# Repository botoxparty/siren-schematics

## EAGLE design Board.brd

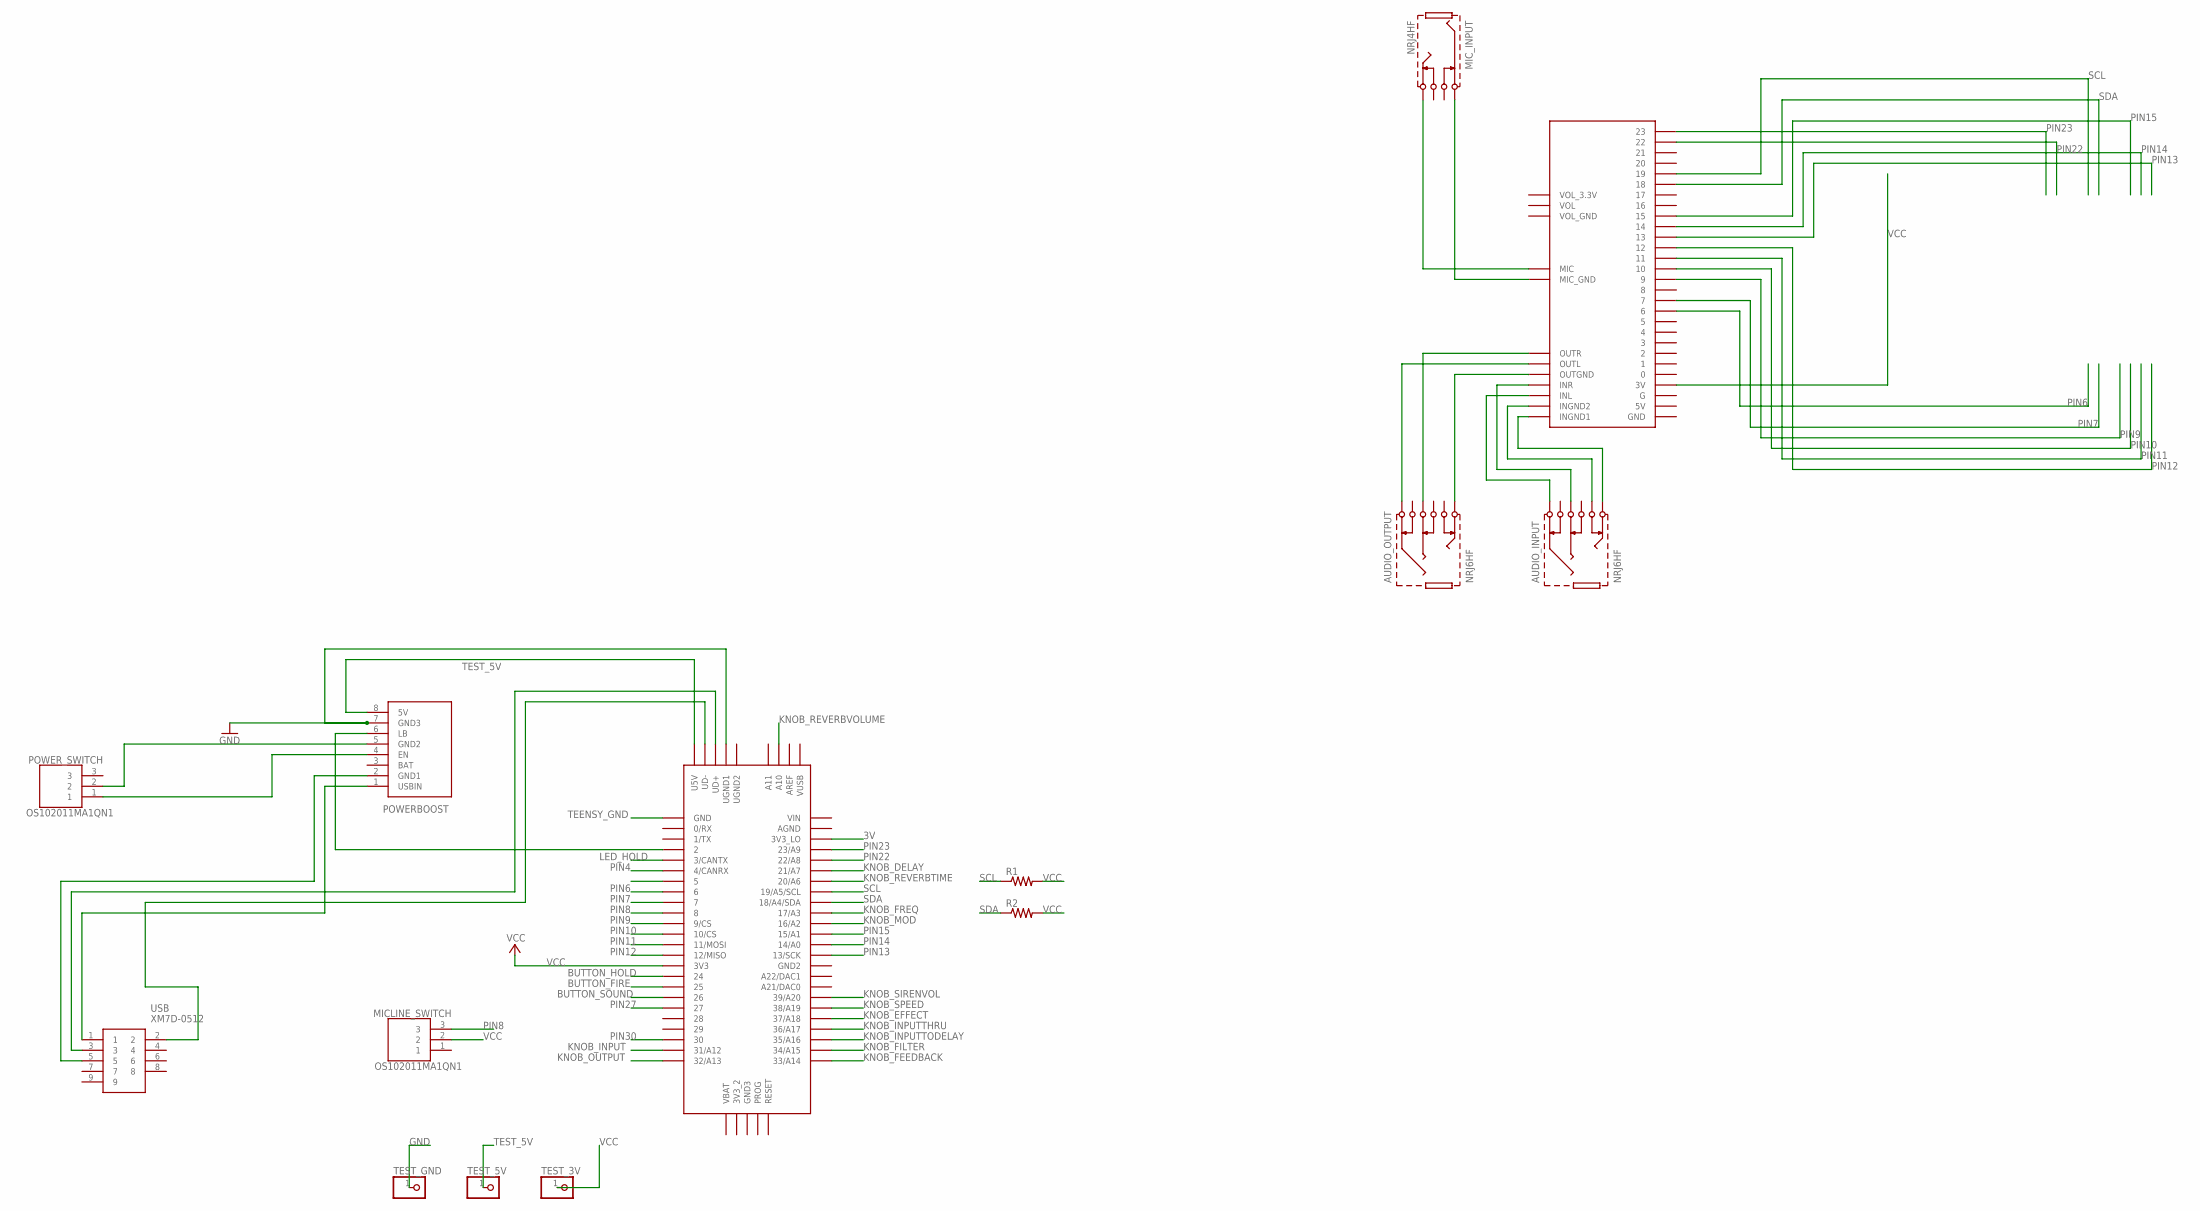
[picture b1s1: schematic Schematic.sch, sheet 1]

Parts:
AUDIO_INPUT: NRJ6HF
AUDIO_OUTPUT: NRJ6HF
MICLINE_SWITCH: OS102011MA1QN1
MIC_INPUT: NRJ4HF
POWER_SWITCH: OS102011MA1QN1
R1, R2: R-US_0207/10; 0207/10
TEENSY: TEENSY_3.5/3.6
TEST_3V, TEST_5V: PINHD-1X1; 1X01
TEST_GND: PINHD-1X1; 1X01
U$2: POWERBOOST500C; POWERBOOST500
U$5: AUDIOSHIELD
USB: XM7D-0512; XM7D0512

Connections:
3V: TEENSY.3V3_LO
BUTTON_FIRE: TEENSY.25; also elsewhere on the board
BUTTON_HOLD: TEENSY.24; also elsewhere on the board
BUTTON_SOUND: TEENSY.26; also elsewhere on the board
GND: TEENSY.UGND1, TEST_GND.1, U$2.7 (GND3); also elsewhere on the board
KNOB_DELAY: TEENSY.21/A7; also elsewhere on the board
KNOB_EFFECT: TEENSY.37/A18; also elsewhere on the board
KNOB_FEEDBACK: TEENSY.33/A14; also elsewhere on the board
KNOB_FILTER: TEENSY.34/A15; also elsewhere on the board
KNOB_FREQ: TEENSY.17/A3; also elsewhere on the board
KNOB_INPUT: TEENSY.31/A12; also elsewhere on the board
KNOB_INPUTTHRU: TEENSY.36/A17; also elsewhere on the board
KNOB_INPUTTODELAY: TEENSY.35/A16; also elsewhere on the board
KNOB_MOD: TEENSY.16/A2; also elsewhere on the board
KNOB_OUTPUT: TEENSY.32/A13; also elsewhere on the board
KNOB_REVERBTIME: TEENSY.20/A6; also elsewhere on the board
KNOB_REVERBVOLUME: TEENSY.A10; also elsewhere on the board
KNOB_SIRENVOL: TEENSY.39/A20; also elsewhere on the board
KNOB_SPEED: TEENSY.38/A19; also elsewhere on the board
LED_HOLD: TEENSY.3/CANTX; also elsewhere on the board
unnamed: U$2.1 (USBIN), USB.1
unnamed: U$2.2 (GND1), USB.5
unnamed: TEENSY.UD-, USB.2
unnamed: TEENSY.UD+, USB.3
unnamed: MIC_INPUT.SLEEVE, U$5.GND_MIC (MIC_GND)
unnamed: MIC_INPUT.TIP, U$5.MIC
unnamed: AUDIO_OUTPUT.TIP, U$5.OUTGND
unnamed: AUDIO_INPUT.SLEEVE, U$5.INL
unnamed: AUDIO_OUTPUT.RING, U$5.OUTR
unnamed: AUDIO_INPUT.TIP, U$5.INGND1
unnamed: AUDIO_INPUT.TIP-S, U$5.INGND2
unnamed: AUDIO_INPUT.RING, U$5.INR
unnamed: AUDIO_OUTPUT.SLEEVE, U$5.OUTL
unnamed: TEENSY.2, U$2.6 (LB)
unnamed: POWER_SWITCH.1, U$2.4 (EN)
unnamed: POWER_SWITCH.2, U$2.5 (GND2)
PIN4: TEENSY.4/CANRX; also elsewhere on the board
PIN5: TEENSY.5; also elsewhere on the board
PIN6: TEENSY.6, U$5.6
PIN7: TEENSY.7, U$5.7
PIN8: MICLINE_SWITCH.3, TEENSY.8
PIN9: TEENSY.9/CS, U$5.9
PIN10: TEENSY.10/CS, U$5.10
PIN11: TEENSY.11/MOSI, U$5.11
PIN12: TEENSY.12/MISO, U$5.12
PIN13: TEENSY.13/SCK, U$5.13
PIN14: TEENSY.14/A0, U$5.14
PIN15: TEENSY.15/A1, U$5.15
PIN22: TEENSY.22/A8, U$5.22
PIN23: TEENSY.23/A9, U$5.23
PIN27: TEENSY.27; also elsewhere on the board
PIN30: TEENSY.30; also elsewhere on the board
SCL: R1.1, TEENSY.19/A5/SCL, U$5.19; also elsewhere on the board
SDA: R2.1, TEENSY.18/A4/SDA, U$5.18; also elsewhere on the board
TEENSY_GND: TEENSY.GND
TEST_5V: TEENSY.U5V, TEST_5V.1, U$2.8 (5V)
VCC: MICLINE_SWITCH.2, R1.2, R2.2, TEENSY.3V3, TEST_3V.1, U$5.3V; also elsewhere on the board

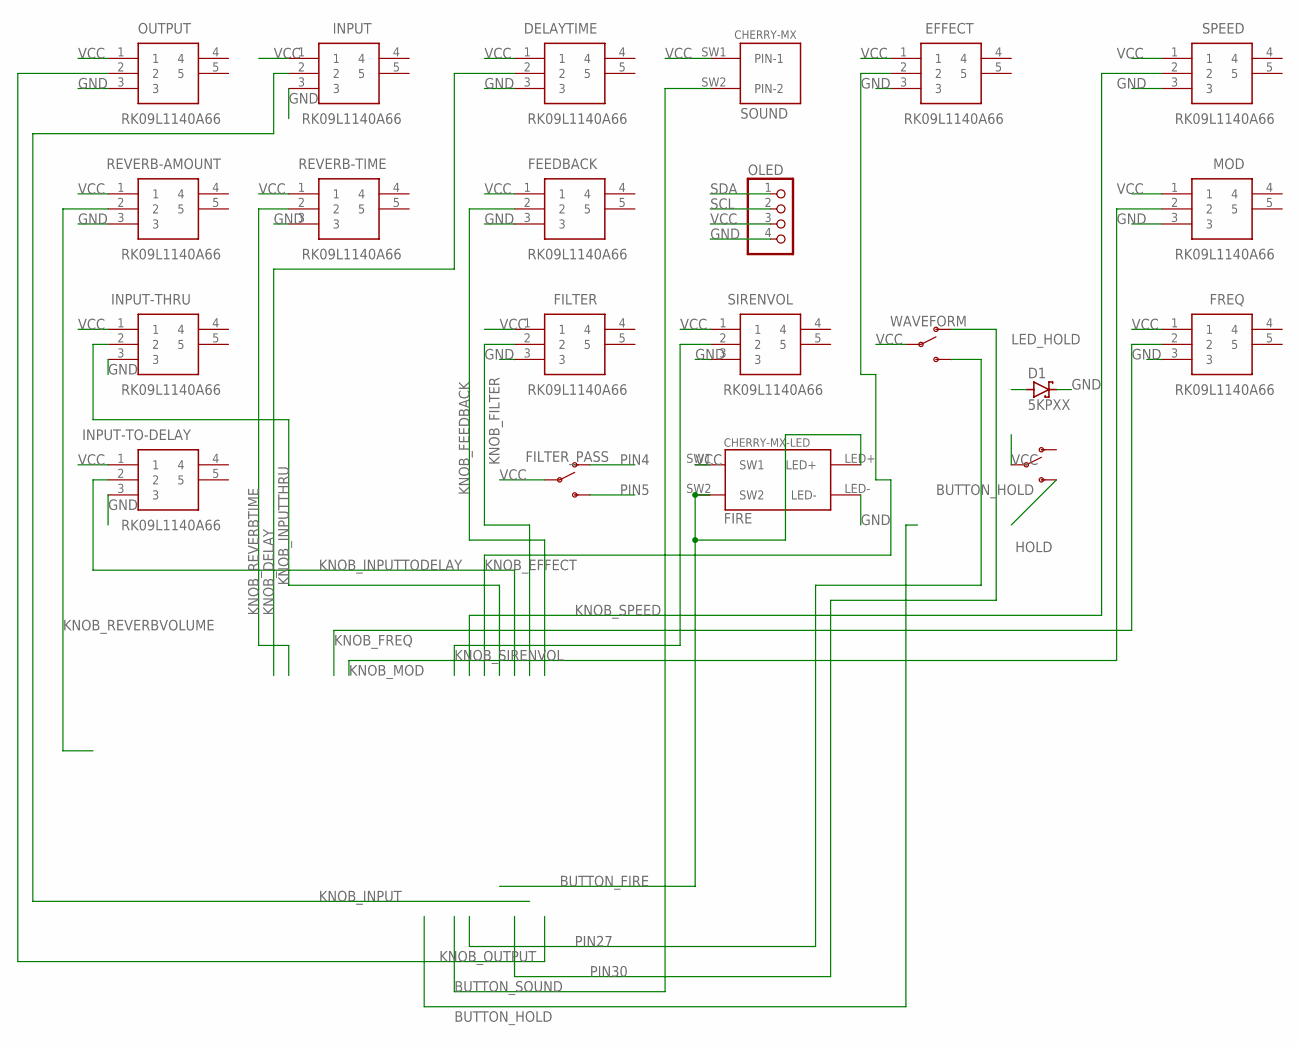
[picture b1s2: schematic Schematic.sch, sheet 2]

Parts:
D1: 5KPXX; P6T15
DELAYTIME: RK09L1140A66
EFFECT: RK09L1140A66
FEEDBACK: RK09L1140A66
FILTER: RK09L1140A66
FILTER_PASS: SWITCH-SPDT-PTH-11.6X4.0MM-LOCK; SWITCH_SPDT_PTH_11.6X4.0MM_LOCK
FIRE: CHERRY-MX-LED
FREQ: RK09L1140A66
HOLD: SWITCH-SPDT-PTH-11.6X4.0MM-LOCK; SWITCH_SPDT_PTH_11.6X4.0MM_LOCK
INPUT: RK09L1140A66
INPUT-THRU: RK09L1140A66
INPUT-TO-DELAY: RK09L1140A66
MOD: RK09L1140A66
OLED: PINHD-1X4; 1X04
OUTPUT: RK09L1140A66
REVERB-AMOUNT: RK09L1140A66
REVERB-TIME: RK09L1140A66
SIRENVOL: RK09L1140A66
SOUND: CHERRY-MX
SPEED: RK09L1140A66
WAVEFORM: SWITCH-SPDT-PTH-11.6X4.0MM-LOCK; SWITCH_SPDT_PTH_11.6X4.0MM_LOCK

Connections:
BUTTON_FIRE: FIRE.LED+, FIRE.SW2; also elsewhere on the board
BUTTON_HOLD: HOLD.3 (S); also elsewhere on the board
BUTTON_SOUND: SOUND.SW2 (PIN-2); also elsewhere on the board
GND: D1.C, DELAYTIME.3, EFFECT.3, FEEDBACK.3, FILTER.3, FIRE.LED-, FREQ.3, INPUT.3, INPUT-THRU.3, INPUT-TO-DELAY.3, MOD.3, OLED.4, OUTPUT.3, REVERB-AMOUNT.3, REVERB-TIME.3, SIRENVOL.3, SPEED.3; also elsewhere on the board
KNOB_DELAY: DELAYTIME.2; also elsewhere on the board
KNOB_EFFECT: EFFECT.2; also elsewhere on the board
KNOB_FEEDBACK: FEEDBACK.2; also elsewhere on the board
KNOB_FILTER: FILTER.2; also elsewhere on the board
KNOB_FREQ: FREQ.2; also elsewhere on the board
KNOB_INPUT: INPUT.2; also elsewhere on the board
KNOB_INPUTTHRU: INPUT-THRU.2; also elsewhere on the board
KNOB_INPUTTODELAY: INPUT-TO-DELAY.2; also elsewhere on the board
KNOB_MOD: MOD.2; also elsewhere on the board
KNOB_OUTPUT: OUTPUT.2; also elsewhere on the board
KNOB_REVERBTIME: REVERB-TIME.2; also elsewhere on the board
KNOB_REVERBVOLUME: REVERB-AMOUNT.2; also elsewhere on the board
KNOB_SIRENVOL: SIRENVOL.2; also elsewhere on the board
KNOB_SPEED: SPEED.2; also elsewhere on the board
LED_HOLD: D1.A; also elsewhere on the board
PIN4: FILTER_PASS.1 (O); also elsewhere on the board
PIN5: FILTER_PASS.3 (S); also elsewhere on the board
PIN27: WAVEFORM.3 (S); also elsewhere on the board
PIN30: WAVEFORM.1 (O); also elsewhere on the board
SCL: OLED.2; also elsewhere on the board
SDA: OLED.1; also elsewhere on the board
VCC: DELAYTIME.1, EFFECT.1, FEEDBACK.1, FILTER.1, FILTER_PASS.2, FIRE.SW1, FREQ.1, HOLD.2, INPUT.1, INPUT-THRU.1, INPUT-TO-DELAY.1, MOD.1, OLED.3, OUTPUT.1, REVERB-AMOUNT.1, REVERB-TIME.1, SIRENVOL.1, SOUND.SW1 (PIN-1), SPEED.1, WAVEFORM.2; also elsewhere on the board

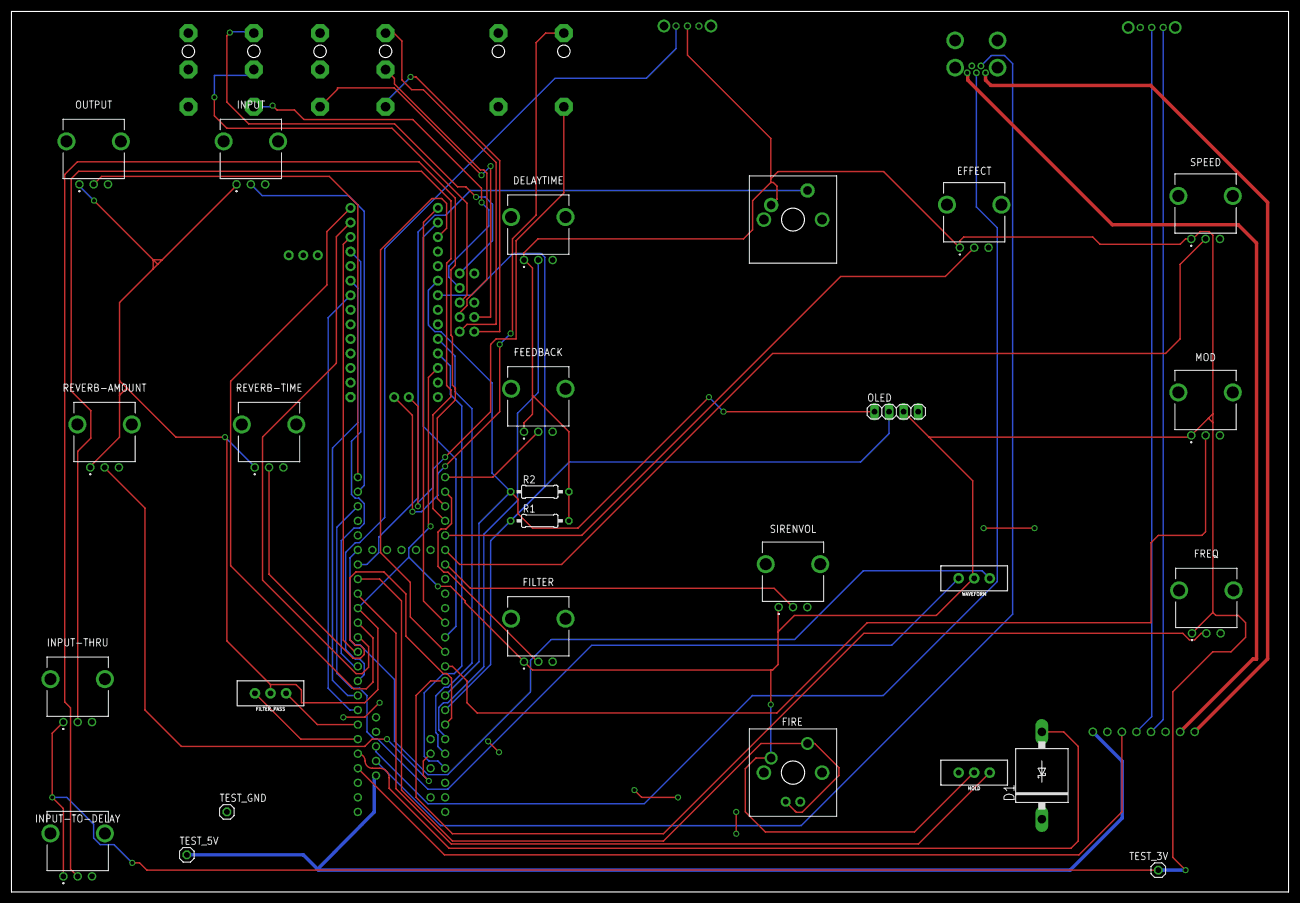
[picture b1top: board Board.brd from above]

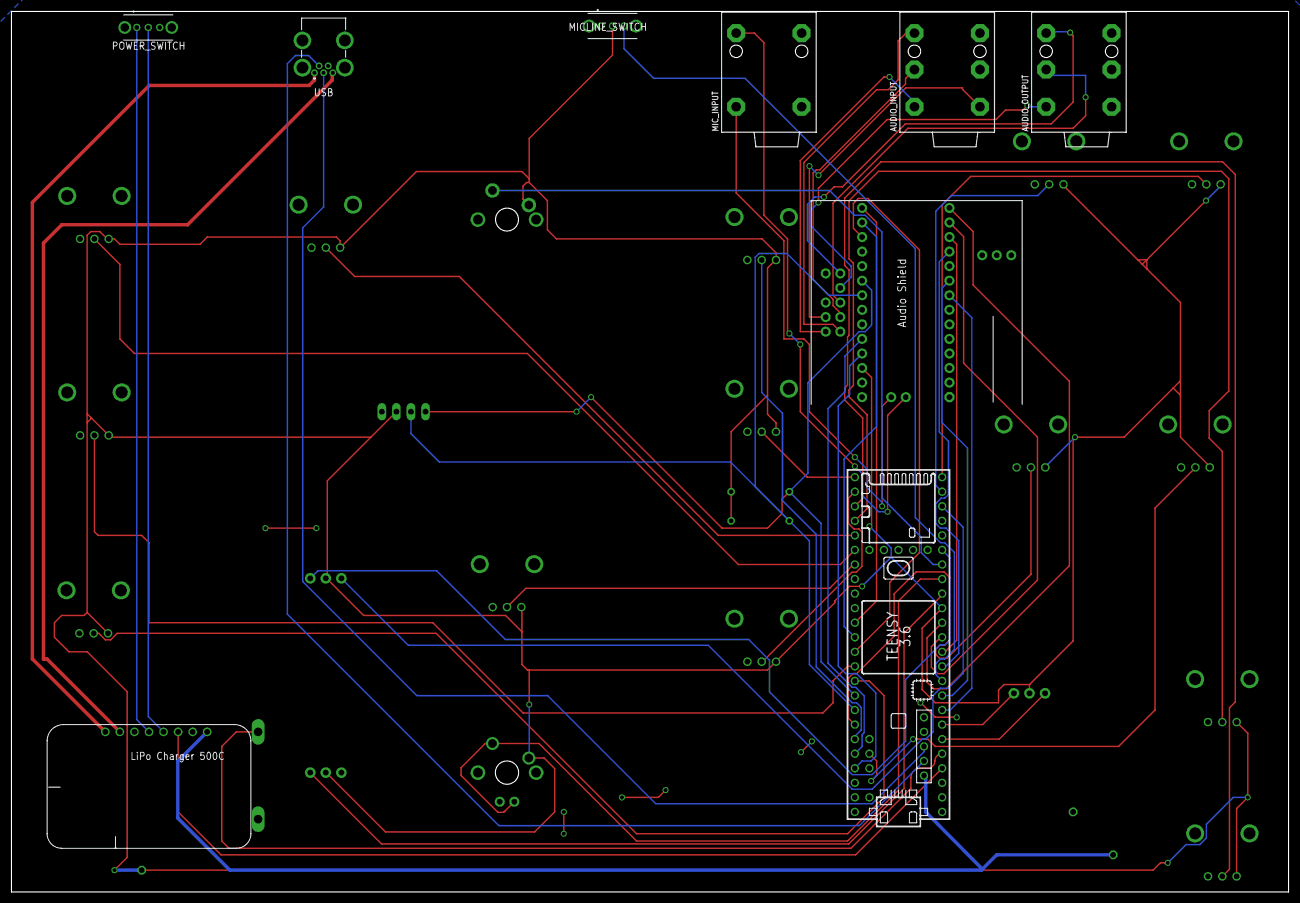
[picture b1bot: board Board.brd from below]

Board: 2 copper layers, 222.9 x 153.7 mm, 35 parts (9 on the bottom side), 55 nets.

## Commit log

2019-02-02 board with routing

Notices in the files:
parts and their libraries:
audio: Copyright (C) 2008, Bob Starr
SparkFun-Switches: Licensing: Creative Commons ShareAlike 4.0 International - https://creativecommons.org/licenses/by-sa/4.0
